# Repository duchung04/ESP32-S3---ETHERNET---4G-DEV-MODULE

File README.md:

ESP32-S3---ETHERNET---4G-DEV-MODULE

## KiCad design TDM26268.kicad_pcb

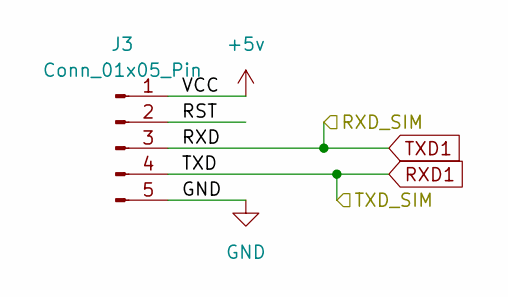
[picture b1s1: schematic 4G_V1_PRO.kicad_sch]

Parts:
J3: Conn_01x05_Pin; PinHeader_1x05_P2.54mm_Vertical

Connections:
+5v: J3.1; also elsewhere on the board
/4G_V1_PRO/RST: J3.2
GND: J3.5; also elsewhere on the board
RXD1: J3.4; also elsewhere on the board
TXD1: J3.3; also elsewhere on the board

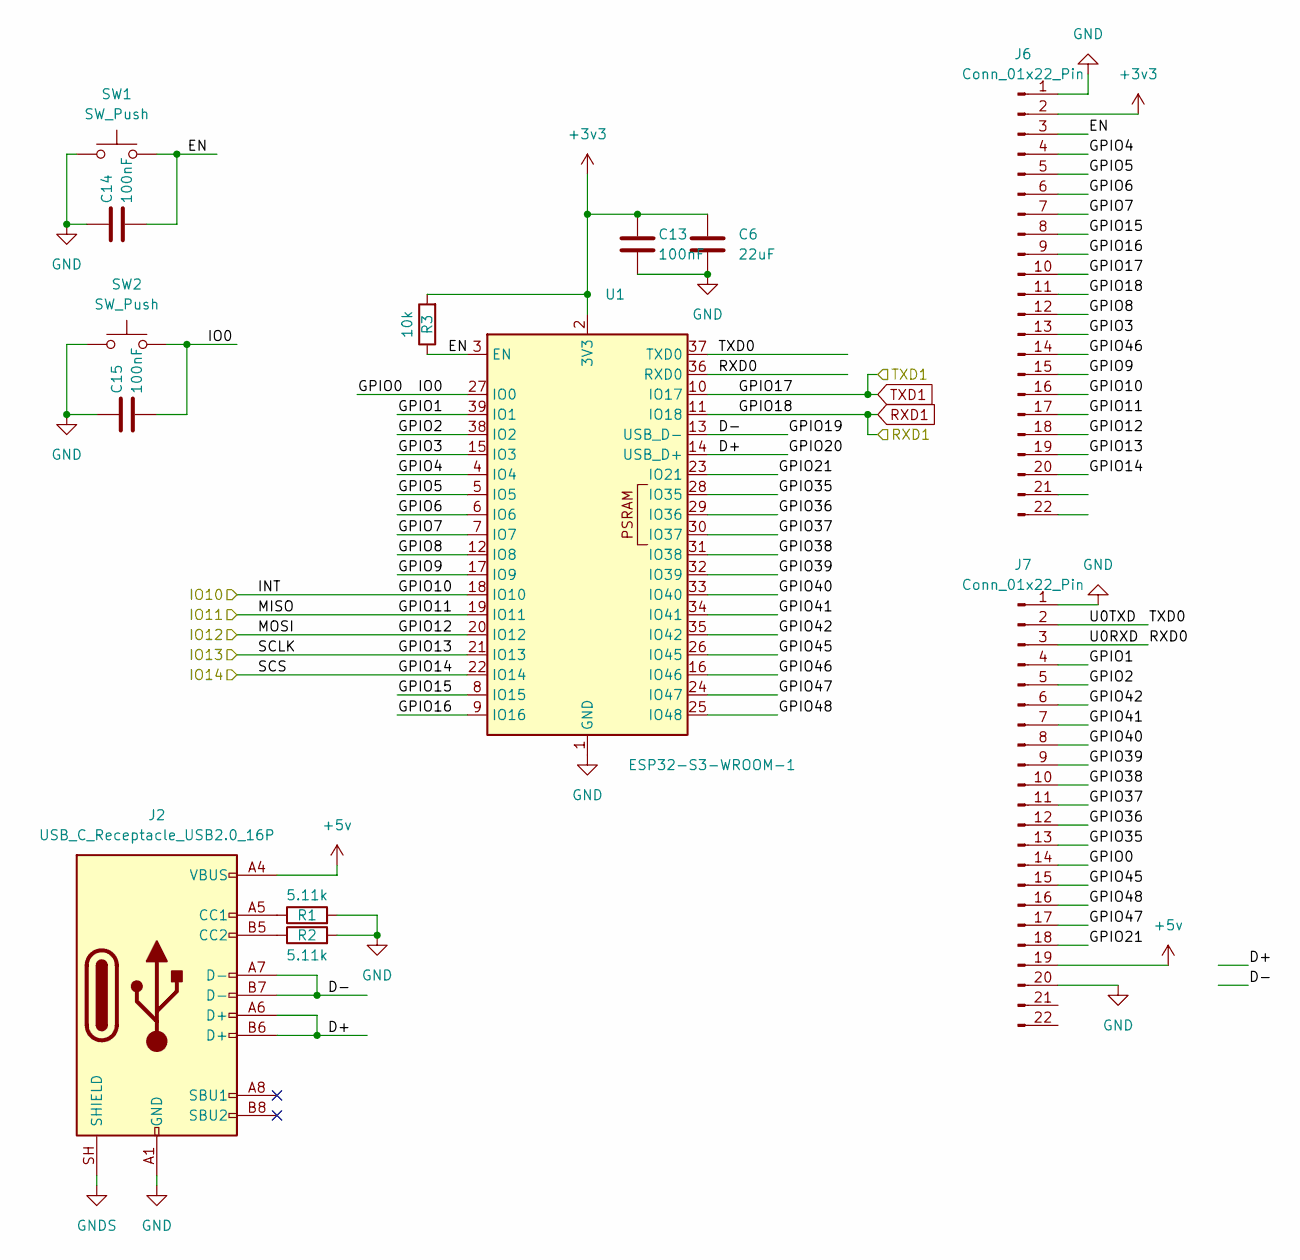
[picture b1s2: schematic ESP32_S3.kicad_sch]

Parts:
C6: 22uF; C_0805_2012Metric
C13, C14, C15: 100nF; C_0603_1608Metric
J2: USB_C_Receptacle_USB2.0_16P; USB_C_Receptacle_HCTL_HC-TYPE-C-16P-01A
J6, J7: Conn_01x22_Pin; PinHeader_1x20_P2.54mm_Vertical
R1, R2: 5.11k; R_0603_1608Metric
R3: 10k; R_0603_1608Metric
SW1, SW2: SW_Push; SW_SPST_B3U-1000P
U1: ESP32-S3-WROOM-1

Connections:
+3v3: C6.1, C13.1, J6.2, R3.2, U1.2 (3V3); also elsewhere on the board
+5v: J2.A4 (VBUS), J2.A9 (VBUS), J2.B4 (VBUS), J2.B9 (VBUS), J7.19; also elsewhere on the board
/ESP32_S3/D+: J2.A6 (D+), J2.B6 (D+), U1.14 (USB_D+)
/ESP32_S3/D-: J2.A7 (D-), J2.B7 (D-), U1.13 (USB_D-)
/ESP32_S3/EN: C14.2, J6.3, R3.1, SW1.2, U1.3 (EN)
/ESP32_S3/GPIO0: C15.2, J7.14, SW2.2, U1.27 (IO0)
/ESP32_S3/GPIO1: J7.4, U1.39 (IO1)
/ESP32_S3/GPIO2: J7.5, U1.38 (IO2)
/ESP32_S3/GPIO3: J6.13, U1.15 (IO3)
/ESP32_S3/GPIO4: J6.4, U1.4 (IO4)
/ESP32_S3/GPIO5: J6.5, U1.5 (IO5)
/ESP32_S3/GPIO6: J6.6, U1.6 (IO6)
/ESP32_S3/GPIO7: J6.7, U1.7 (IO7)
/ESP32_S3/GPIO8: J6.12, U1.12 (IO8)
/ESP32_S3/GPIO9: J6.15, U1.17 (IO9)
/ESP32_S3/GPIO10: J6.16, U1.18 (IO10); also elsewhere on the board
/ESP32_S3/GPIO11: J6.17, U1.19 (IO11); also elsewhere on the board
/ESP32_S3/GPIO12: J6.18, U1.20 (IO12); also elsewhere on the board
/ESP32_S3/GPIO13: J6.19, U1.21 (IO13); also elsewhere on the board
/ESP32_S3/GPIO14: J6.20, U1.22 (IO14); also elsewhere on the board
/ESP32_S3/GPIO15: J6.8, U1.8 (IO15)
/ESP32_S3/GPIO16: J6.9, U1.9 (IO16)
/ESP32_S3/GPIO21: J7.18, U1.23 (IO21)
/ESP32_S3/GPIO35: J7.13, U1.28 (IO35)
/ESP32_S3/GPIO36: J7.12, U1.29 (IO36)
/ESP32_S3/GPIO37: J7.11, U1.30 (IO37)
/ESP32_S3/GPIO38: J7.10, U1.31 (IO38)
/ESP32_S3/GPIO39: J7.9, U1.32 (IO39)
/ESP32_S3/GPIO40: J7.8, U1.33 (IO40)
/ESP32_S3/GPIO41: J7.7, U1.34 (IO41)
/ESP32_S3/GPIO42: J7.6, U1.35 (IO42)
/ESP32_S3/GPIO45: J7.15, U1.26 (IO45)
/ESP32_S3/GPIO46: J6.14, U1.16 (IO46)
/ESP32_S3/GPIO47: J7.17, U1.24 (IO47)
/ESP32_S3/GPIO48: J7.16, U1.25 (IO48)
/ESP32_S3/RXD0: J7.3, U1.36 (RXD0)
/ESP32_S3/TXD0: J7.2, U1.37 (TXD0)
GND: C6.2, C13.2, C14.1, C15.1, J2.A1 (GND), J2.A12 (GND), J2.B1 (GND), J2.B12 (GND), J6.1, J7.1, J7.20, R1.2, R2.2, SW1.1, SW2.1, U1.1 (GND), U1.40 (GND), U1.41 (GND); also elsewhere on the board
GNDS: J2.SH (SHIELD); also elsewhere on the board
unnamed: J2.A5 (CC1), R1.1
unnamed: J2.B5 (CC2), R2.1
RXD1: J6.11, U1.11 (IO18); also elsewhere on the board
TXD1: J6.10, U1.10 (IO17); also elsewhere on the board

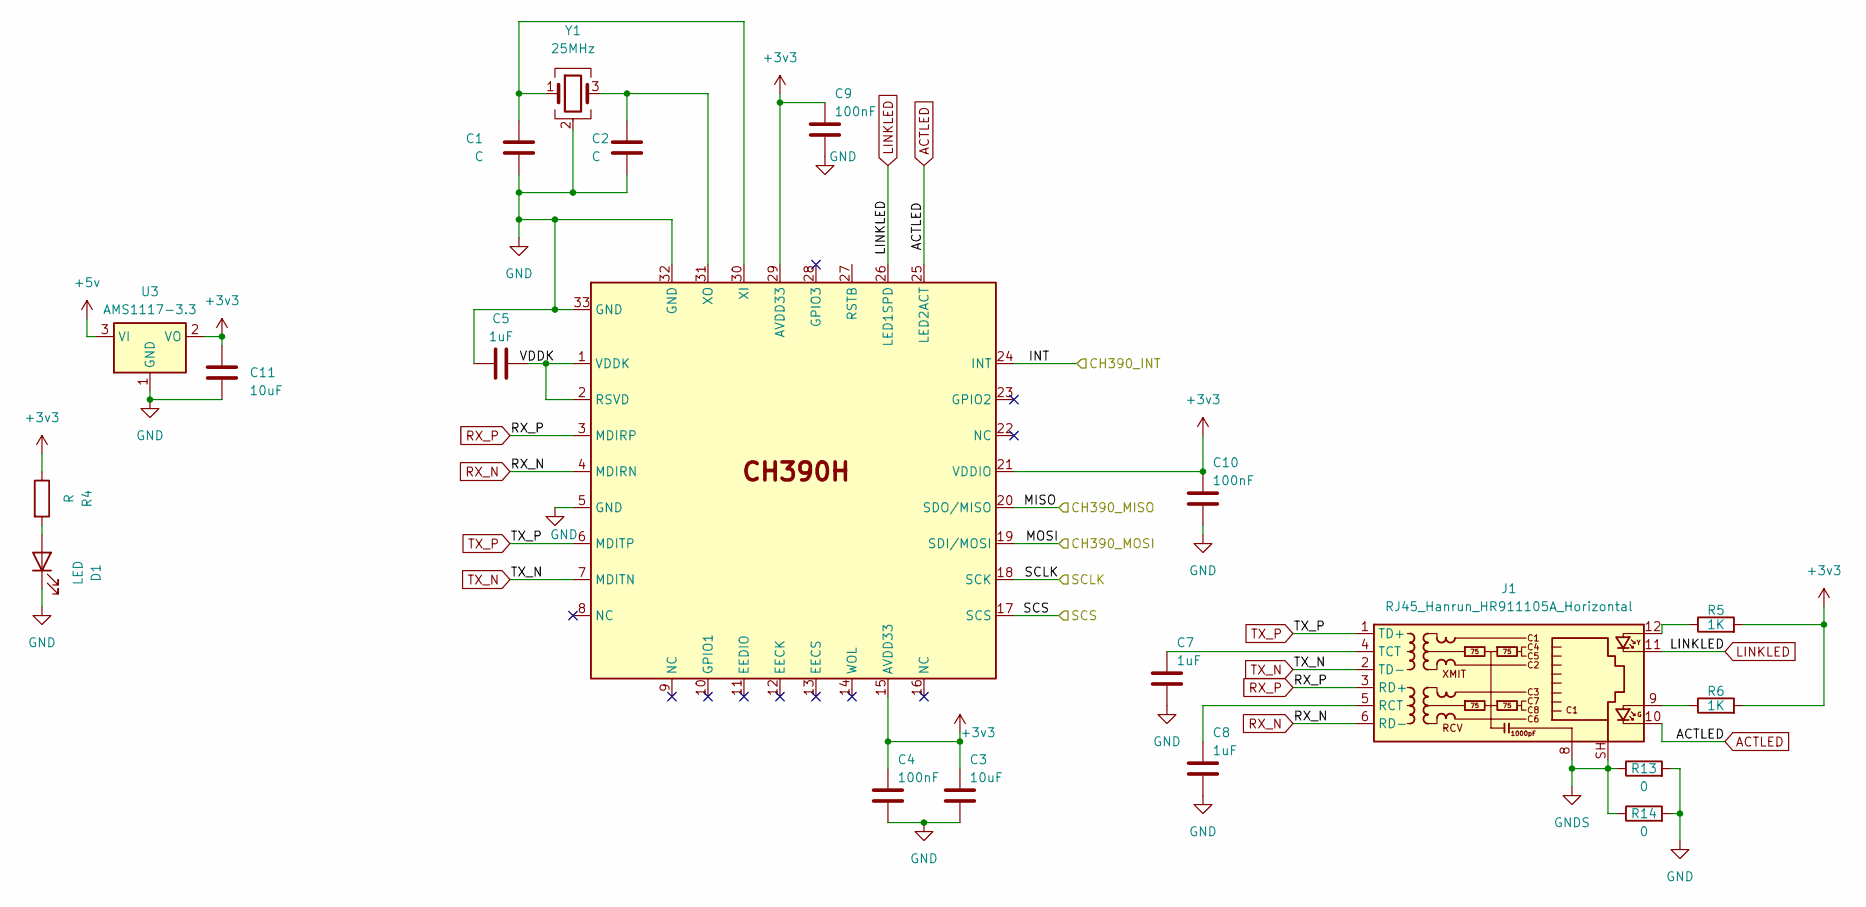
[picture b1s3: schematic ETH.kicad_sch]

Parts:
C1, C2: C; C_0603_1608Metric
C3: 10uF; C_0805_2012Metric
C4, C9, C10: 100nF; C_0603_1608Metric
C5, C7, C8: 1uF; C_0603_1608Metric
C11: 10uF; C_0805_2012Metric_Pad1.18x1.45mm_HandSolder
D1: LED; LED_0603_1608Metric
J1: RJ45_Hanrun_HR911105A_Horizontal
R4: R; R_0603_1608Metric
R5, R6: 1K; R_0603_1608Metric
R13, R14: 0; R_1206_3216Metric
U3: AMS1117-3.3; SOT-223-3_TabPin2
U4: CH390D; QFN-32-1EP_5x5mm_P0.5mm_EP3.3x3.3mm_ThermalVias
Y1: 25MHz; Crystal_SMD_3225-4Pin_3.2x2.5mm

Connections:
+3v3: C3.1, C4.1, C9.1, C10.1, C11.1, R4.1, R5.2, R6.2, U3.2 (VO), U4.15 (AVDD33), U4.21 (VDDIO), U4.29 (AVDD33); also elsewhere on the board
+5v: U3.3 (VI); also elsewhere on the board
/ESP32_S3/GPIO10: U4.24 (INT); also elsewhere on the board
/ESP32_S3/GPIO11: U4.20 (SDO/MISO); also elsewhere on the board
/ESP32_S3/GPIO12: U4.19 (SDI/MOSI); also elsewhere on the board
/ESP32_S3/GPIO13: U4.18 (SCK); also elsewhere on the board
/ESP32_S3/GPIO14: U4.17 (SCS); also elsewhere on the board
/ETH/VDDK: C5.2, U4.1 (VDDK), U4.2 (RSVD)
ACTLED: J1.10, U4.25 (LED2ACT)
GND: C1.2, C2.2, C3.2, C4.2, C5.1, C7.2, C8.2, C9.2, C10.2, C11.2, D1.1 (K), R13.2, R14.2, U3.1 (GND), U4.5 (GND), U4.32 (GND), U4.33 (GND), Y1.2 (G), Y1.4 (G); also elsewhere on the board
GNDS: J1.8, J1.SH, R13.1, R14.1; also elsewhere on the board
LINKLED: J1.11, U4.26 (LED1SPD)
unnamed: D1.2 (A), R4.2
unnamed: J1.9, R6.1
unnamed: J1.12, R5.1
unnamed: C8.1, J1.5 (RCT)
unnamed: C7.1, J1.4 (TCT)
unnamed: C1.1, U4.30 (XI), Y1.1
unnamed: C2.1, U4.31 (XO), Y1.3
RX_N: J1.6 (RD-), U4.4 (MDIRN)
RX_P: J1.3 (RD+), U4.3 (MDIRP)
TX_N: J1.2 (TD-), U4.7 (MDITN)
TX_P: J1.1 (TD+), U4.6 (MDITP)

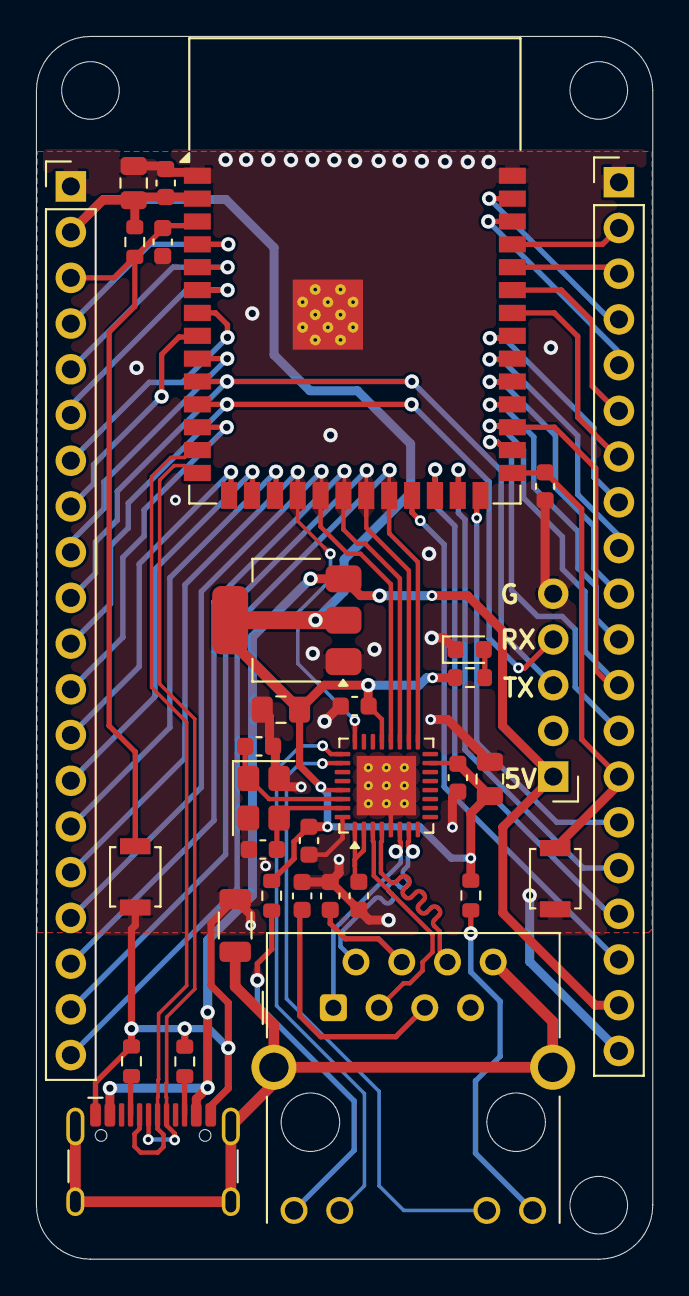
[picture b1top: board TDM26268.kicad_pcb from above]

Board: 2 copper layers, 34.2 x 67.9 mm, 33 parts (0 on the bottom side), 57 nets.
